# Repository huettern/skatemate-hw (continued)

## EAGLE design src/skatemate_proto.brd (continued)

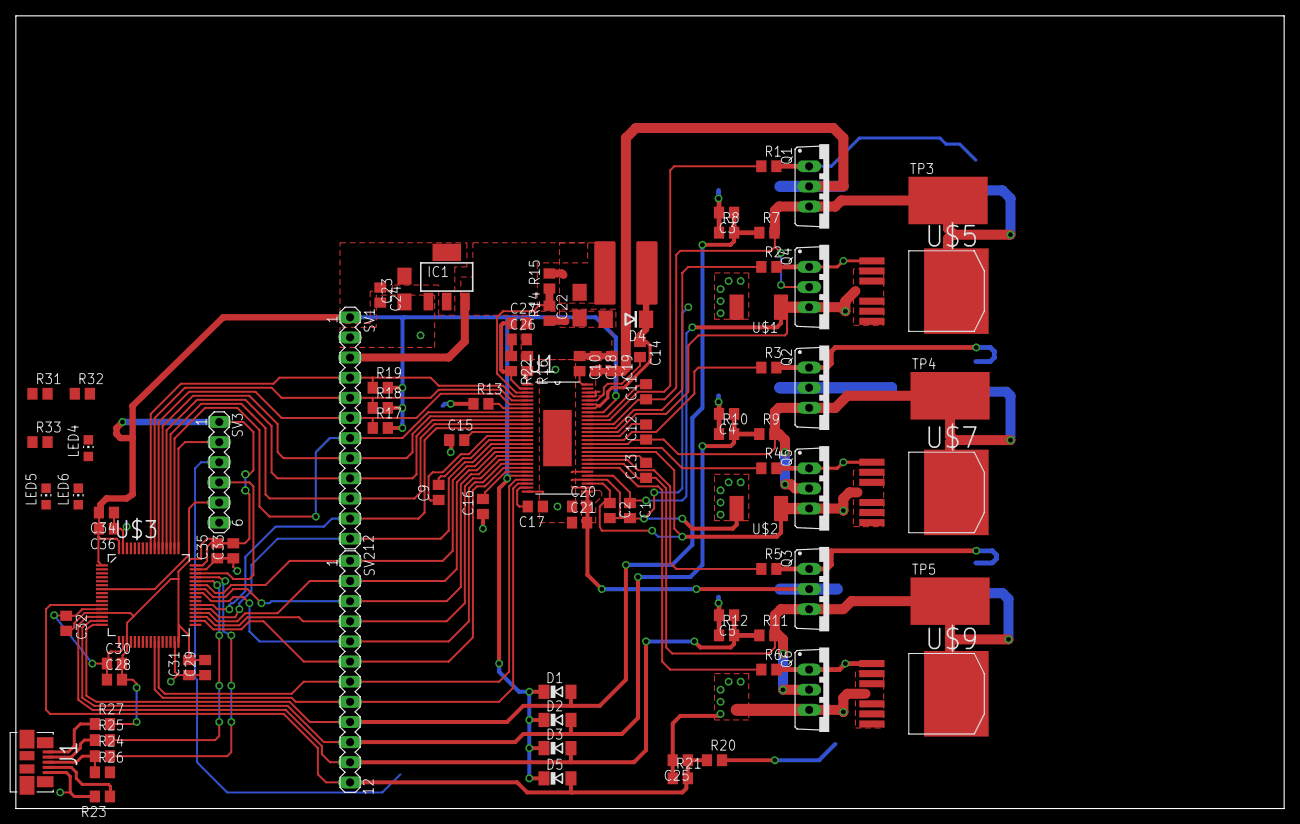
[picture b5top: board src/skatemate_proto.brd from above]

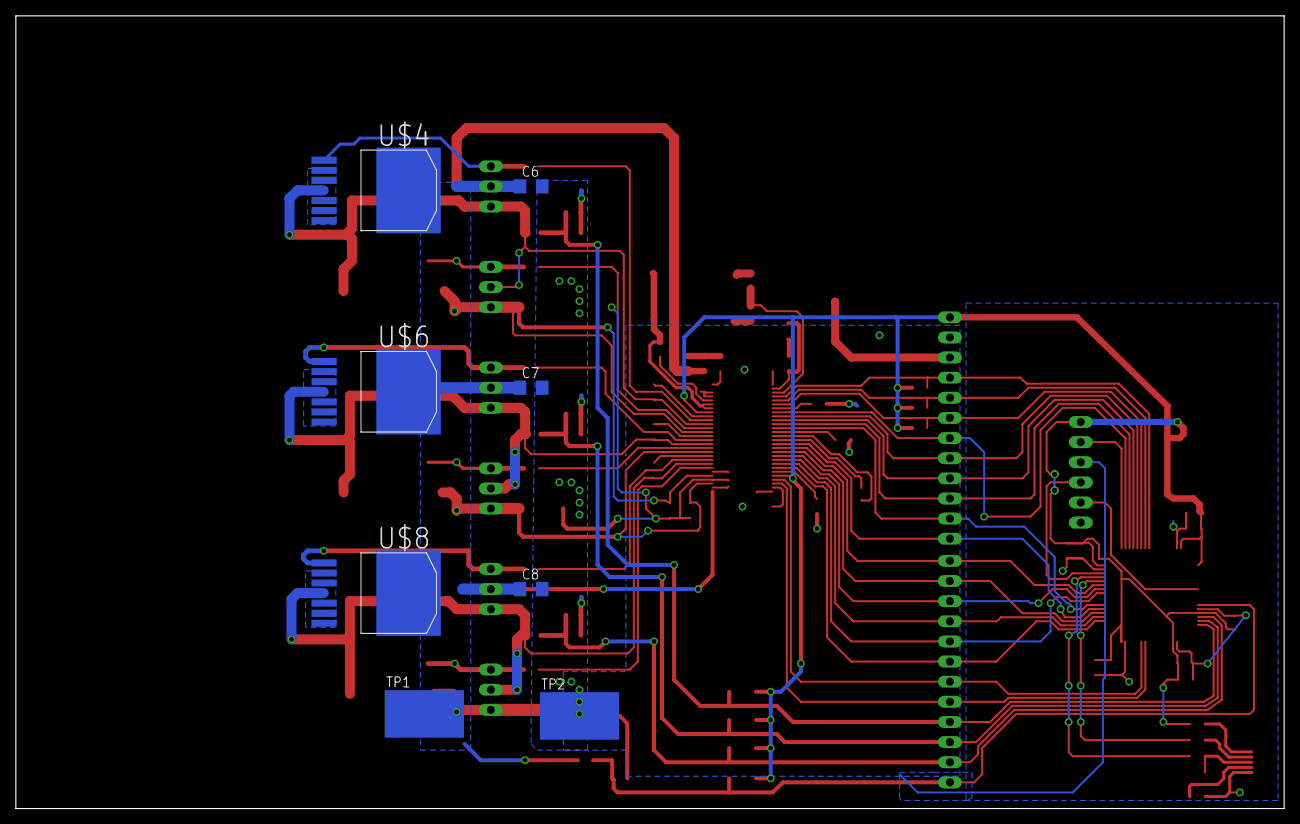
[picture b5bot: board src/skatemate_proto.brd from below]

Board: 2 copper layers, 160.0 x 100.0 mm, 101 parts (8 on the bottom side), 67 nets.

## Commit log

2017-02-28 First prototype schematics
2017-03-01 TP components added in lib
2017-03-01 starting layout
2017-03-01 Further routing
2017-03-02 Test
2017-03-03 links es bezzeli
2017-03-03 Leistungsstufe weiter geroutet
2017-03-07 Epty BM sch and brd file
2017-03-08 First Version Schematic(Layout wip)
2017-03-08 Add a library
2017-03-08 Add 3.3V Step-Down Converter
2017-03-09 Version 0.1 Layout
2017-03-12 V0.9 Layout and Schematic ready for review and version jump to 1.0.
2017-03-12 Revert "V0.9 Layout and Schematic ready for review and version jump to 1.0."
    This reverts commit 28fefd69818988460ab9c4da467096be04e20f85.
2017-03-13 Large junk of routing logic
2017-03-14 Added uC
2017-03-16 more digital layout
2017-03-16 library
2017-03-16 lqfp64 and layout
2017-03-16 more layout
2017-03-23 Verdrohtet
2017-03-23 IRFS7534 added
2017-03-28 Library update / Schematic 5V Buck Converter Delete
2017-03-28 Worked at the Schematic
2017-03-29 Upload it, that i can work at the PC
2017-03-29 schematic ready to layout
2017-03-30 Layout_Testplatine_fertig_1
    FET's zusätzlich verbunden
2017-03-30 Added LED and crystal
2017-04-03 just updating my pc
2017-04-03 layout update
2017-04-05 Just GND Layout missing
2017-04-06 Schematic PDF uplaod
2017-04-08 Create pdf and added cangelist
2017-04-08 Folder rename
2017-04-08 documentation
2017-04-09 just for fun.... nooot
    changed some parts
2017-04-09 V0.1 finished
2017-04-09 Finished version v0.2
2017-04-19 added USART TX/RX labels
2017-04-21 new todo
2017-04-26 mc new file hirarchy and revision
    Created version v0.2 with following changes:
    done - 4.7 uF Caps C18 and C20 change to 1206
    done - C10 used 10nF
    done - 1 uF Caps C17 (and others??) change to 1206
    done - R16 used 200k
    done - R22 used 16k
2017-04-26 layouting on v0.2
2017-04-27 Backup commit.
2017-04-28 Öpdeit, Meh gmoolet
2017-04-28 no wiiter gmacht....
    Kondensatoren noch unter IC pflanzen, Stecker Layouten, eine VCC Leitung
    mit 100uF versehen.
2017-05-02 ulp for creating bom
2017-05-02 renumber parts and bom
2017-05-03 Revert "Finished version v0.2"
    This reverts commit a5989fd47d9f9b1588f2c3c09283aac7458017f8.
2017-05-03 Revert "Revert "Finished version v0.2""
    This reverts commit 5ce350199b8ee6846b212b42396474e627ee3767.
2017-05-04 layout before review
2017-05-04 Parts renumber and BOM ULP
2017-05-05 Add RFM module
2017-05-07 It's for my pc
2017-05-07 schematic up to date
2017-05-07 Start with schematic
2017-05-07 little update
2017-05-07 finished all wires and first review
2017-05-07 Extern Print Version 0.1
2017-05-07 next generation
2017-05-08 pretty 45
2017-05-08 Layout angepasst
    C ergänzt
2017-05-08 update save
2017-05-08 backup
2017-05-08 USART3 populated
2017-05-08 finish layout
2017-05-12 Added missing values
2017-05-29 New Version of MagicGlove Print - Rewired the analog part - Smaller Layout alltogether Initial Version of MagicGlove Receiver Print - Some GPIO Pads for anything that might be added
2017-06-11 Receiver Board v1.0 working
2017-06-11 Style
2017-06-11 bm style
